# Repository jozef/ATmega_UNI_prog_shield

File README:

NAME

    ATmega UNI Programming Shield - works with Arduino ISP from examples

DESCRIPTION

    Small shield connecting SPI lines and with RGB led on D7,8,9 pins. In
    addition jumper on the left of ICSP has to be set to e~10→RST so that
    D10 from programming board is connected to reset of programmed
    microcontroller.

SEE ALSO

    https://github.com/jozef/ATmega_UNI,
    https://github.com/jozef/ATmega_UNI_prog_shield,
    https://blog.kutej.net/09/ATmega-UNI-prog-shield

LICENSE

    This is free software & hardware, licensed under the MIT License.

AUTHOR

        Jozef Kutej

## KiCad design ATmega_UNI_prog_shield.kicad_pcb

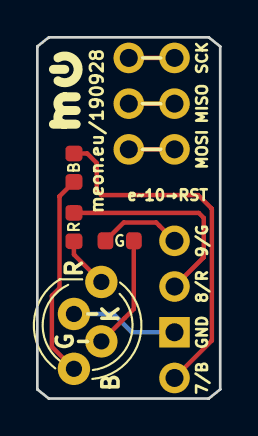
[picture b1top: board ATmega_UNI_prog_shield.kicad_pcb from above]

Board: 2 copper layers, 10.2 x 20.1 mm, 6 parts (0 on the bottom side), 10 nets.

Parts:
D2: LED_RCGB; LED_D5.0mm-4_RGB_Staggered_Pins
J1: Conn_02x03_SPI_RST; PinSocket_2x03_P2.54mm_Vertical_no_lines
J2: Conn_01x04_Prog; PinSocket_1x04_P2.54mm_Vertical_no_lines
R21: R; R_0603_1608Metric_no_lines
R23: G; R_0603_1608Metric_no_lines
R24: B; R_0603_1608Metric_no_lines

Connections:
B: D2.4, R24.1
D7: J2.4, R24.2
D8: J2.2, R21.2
D9: J2.1, R23.2
G: D2.3, R23.1
GND: D2.2, J2.3
MISO-12: J1.3, J1.4
MOSI-11: J1.5, J1.6
R: D2.1, R21.1
SCK-13: J1.1, J1.2

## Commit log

2019-09-29 initial
2019-09-29 fix Pod
